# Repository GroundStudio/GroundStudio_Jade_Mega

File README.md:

GroundStudio Jade Mega
====================================

Get it from [ardushop.ro](https://ardushop.ro/en/development-boards/1937-groundstudio-jade-m1-6427854029508.html)

Explore all the GroundStudio products at [ardushop.ro](https://ardushop.ro/en/37-groundstudio)

Description
-------------------
ATMEGA2560 based development board with 256kBytes of In-System Self-Programmable Flash program memory, 4kBytes EEPROM, 8kBytes Internal SRAM, 15 PWM Channels, 70 Digital Pins including 16 channel 10 bit ADC Pins and HT42B534 for USB comunication.

Contents
-------------------

* [/Documentation](https://github.com/GroundStudio/GroundStudio_Jade_Mega/tree/main/Documentation) -- Pinout.
* [/Hardware](https://github.com/GroundStudio/GroundStudio_Jade_Mega/tree/main/Hardware) -- Schematics, layout.

Versions
-------------------
*(Not all tags shown)*

- [REV 0.1]

License
-------------------

This is released under the [Attribution-ShareAlike 4.0 International (CC BY-SA 4.0)](https://creativecommons.org/licenses/by-sa/4.0/) license.
**You are welcome to use this for commercial purposes.**

Please consider contributing back to this project or others to help the open-source hardware community continue to thrive and grow!

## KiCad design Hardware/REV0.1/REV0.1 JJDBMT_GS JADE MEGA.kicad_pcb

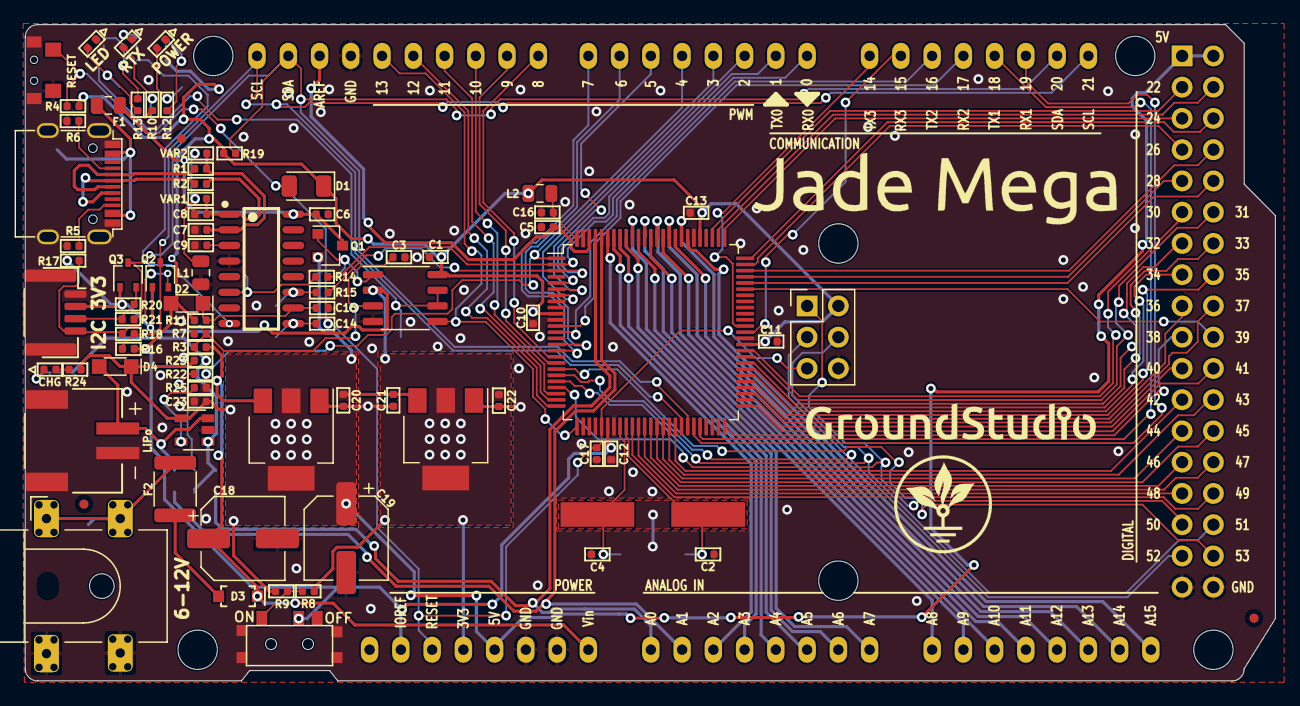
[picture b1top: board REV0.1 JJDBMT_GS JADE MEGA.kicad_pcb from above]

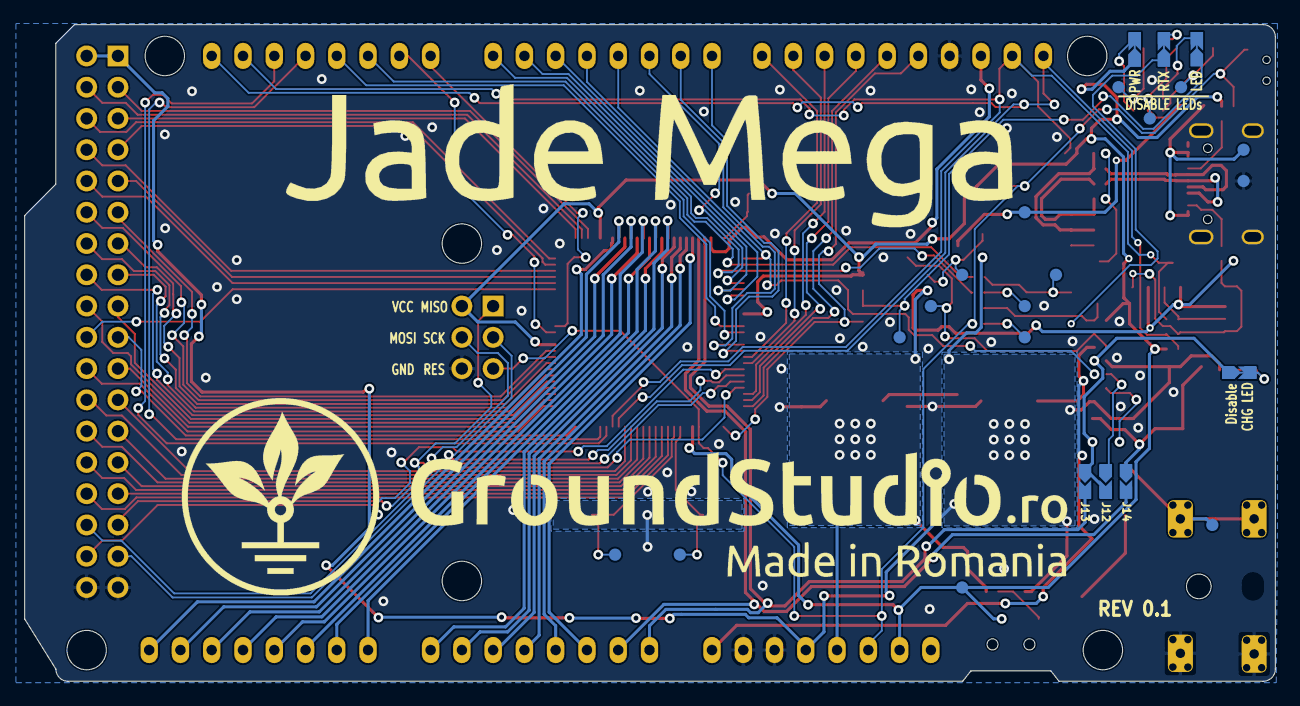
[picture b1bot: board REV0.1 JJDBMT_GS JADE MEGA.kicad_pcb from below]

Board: 2 copper layers, 101.6 x 53.3 mm, 112 parts (7 on the bottom side), 115 nets.

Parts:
C1, C3, C5, C6, C10, C11, C12, C13, C14, C15, C16, C20: C_0402_100nF_16V; C_0402_1005Metric
C2, C4, C17: C_0402_22pF_50V; C_0402_1005Metric
C7, C8: C_0402_47pF_50V; C_0402_1005Metric
C9, C23: C_0402_1uF_10V; C_0402_1005Metric
C18, C19: CP_Elec_6.3x5.4_47uF_25V; CP_Elec_6.3x5.4
C21, C22: C_0402_10uF_10V; C_0402_1005Metric
D1: D_1206_CD1206-S01575; D_1206_3216Metric
D2, D4: SOD-323 SD103AWS; SOD-323
D3: SOD-123 1N4007W; SOD-123
D5: LED_0402_RED; LED_0402_1005Metric
F1: Fuse_0805_MF-PSMF050X-2; Fuse_0805_2012Metric
F2: Fuse_1812_MF-MSMF050-2; Fuse_1812_4532Metric
FID1, FID2, FID3: Fiducial; Fiducial_0.75mm_Mask1.5mm
IC1: SOP-16_150MIL HT42B534-2; SOP-16_150MIL
IC2: SOT23-5 BRCL4054CME; SOT-23-5
J1: RX/TX LED DISABLE; SolderJumper_NC
J2: PWR LED DISABLE; SolderJumper_NC
J3: L LED DISABLE; SolderJumper_NC
J4: Conn_02x03_Odd_Even; PinHeader_2x03_P2.54mm_Vertical_Male
J5: Conn_01x10; PinHeader_1x10_P2.54mm_Vertical_Female
J6, J7, J9, J10, J11: Conn_01x08; PinHeader_1x08_P2.54mm_Vertical_Female
J8: Conn_02x18; PinHeader_2x18_P2.54mm_Vertical_Male
J12: CONNECT & SET D4 HIGH TO READ CHRG LVL ON A0; SolderJumper_NO
J13: CONNECT TO READ CHRG LVL ON A0; SolderJumper_NO
J14: CONNECT TO READ BATT LVL ON A1; SolderJumper_NO
J15: DC-005-5.5-Barr_Jck_SMD; DC-005-5.5-2.0MM-SMD
J16: SolderJumper_NC
L1: L_0805_BLM21PG221SN1D; L_0805_2012Metric
L2: L_0805_SCMI201209X100KT; L_0805_2012Metric
LED1, LED3: LED_0402_GREEN; LED_0402_1005Metric
LED2: LED_0402_RED; LED_0402_1005Metric
Q1: SOT-23 IRLML6402; SOT-23
Q2, Q3: SOT-323 2N7002PW; SOT-323_SC-70
R1, R2: R_0402_33; R_0402_1005Metric
R3, R4, R7: R_0402_10k; R_0402_1005Metric
R5, R6: R_0402_5.1k; R_0402_1005Metric
R8: DNP; R_0402_1005Metric
R9, R11, R18, R21: R_0402_0; R_0402_1005Metric
R10, R12, R13, R24: R_0402_20k; R_0402_1005Metric
R14, R15: R_0402_1k; R_0402_1005Metric
R16, R17, R19, R20: R_0402_2.2k; R_0402_1005Metric
R22, R25: R_0402_2k; R_0402_1005Metric
R23: R_0402_820k; R_0402_1005Metric
SW1: K3-1296S-E2
SW2: TS24CA
TP1: TP_VBUS; TestPoint
TP2: TP_USB_VCC; TestPoint
TP3: TP_LCMD; TestPoint
TP4: TP_VCC; TestPoint
TP5: TP_CMP; TestPoint
TP6: TP_GATE; TestPoint
TP7: TP_XT1; TestPoint
TP8: TP_USH; TestPoint
TP9: TP_XT2; TestPoint
TP10: TP_RTXL; TestPoint
TP11: TP_DTR; TestPoint
TP12: TP_ONL; TestPoint
TP13: TP_LL; TestPoint
TP14: TP_TX; TestPoint
TP15: TP_RX; TestPoint
TP16: TP_PWRIN; TestPoint
U1: SOP-8_3.9x4.9_P1.27 LM358; SOP-8_3.9x4.9mm_P1.27mm
U2: ATMEGA2560-16AU; TQFP-100_14x14mm_P0.5mm
U3: SOT-223 AMS1117-5.0; SOT-223
U4: SOT-223 AMS1117-3.3; SOT-223
USB1: USB_C 918-418K2023S40001; USB_C_C167321
VAR1, VAR2: R_0402_PS0402V014AT; R_0402_1005Metric
X1: SH_1x04_P1.0_H; SH__1x04_P1.00mm_Horizontal
X2: PH__1x02_P2.0_H; PH__1x02_P2.00mm_Horizontal
Y1: HC49-SMD 5M0-1600A2020; Crystal_HC49-SMD

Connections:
+3V3: C22.1, J9.5, Q2.1, Q3.1, R8.2, R17.1, R20.2, U1.2, U4.2, U4.4, X1.2
+5V: C19.1, C20.1, C21.1, C23.1, D4.1, IC2.4, J8.1, J8.2, J9.4, Q1.2, R9.1, R23.1, R24.2, U3.2, U3.4, U4.3
+BAT: D4.2, IC2.3, J14.1, X2.2
A0: J10.8, J13.2, U2.97
A1: J10.7, J14.2, U2.96
A2: J10.6, U2.95
A3: J10.5, U2.94
A4: J10.4, U2.93
A5: J10.3, U2.92
A6: J10.2, U2.91
A7: J10.1, U2.90
A8: J11.8, U2.89
A9: J11.7, U2.88
A10: J11.6, U2.87
A11: J11.5, U2.86
A12: J11.4, U2.85
A13: J11.3, U2.84
A14: J11.2, U2.83
A15: J11.1, U2.82
AREF: C5.1, J5.3, U2.98
CHRG: IC2.1, J12.2, J13.1, J16.1, R23.2
D2: J6.6, U2.6
D3: J6.5, U2.7
D4: J6.4, R22.1, U2.1
D5: J6.3, U2.5
D6: J6.2, U2.15
D7: J6.1, U2.16
D8: J5.10, U2.17
D9: J5.9, U2.18
D10: J5.8, U2.23
D11: J5.7, U2.24
D12: J5.6, U2.25
D13_SCK: J5.5, U1.5, U2.26
D22: J8.3, U2.78
D23: J8.4, U2.77
D24: J8.5, U2.76
D25: J8.6, U2.75
D26: J8.7, U2.74
D27: J8.8, U2.73
D28: J8.9, U2.72
D29: J8.10, U2.71
D30: J8.11, U2.60
D31: J8.12, U2.59
D32: J8.13, U2.58
D33: J8.14, U2.57
D34: J8.15, U2.56
D35: J8.16, U2.55
D36: J8.17, U2.54
D37: J8.18, U2.53
D38: J8.19, U2.50
D39: J8.20, U2.70
D40: J8.21, U2.52
D41: J8.22, U2.51
D42: J8.23, U2.42
D43: J8.24, U2.41
D44: J8.25, U2.40
D45: J8.26, U2.39
D46: J8.27, U2.38
D47: J8.28, U2.37
D48: J8.29, U2.36
D49: J8.30, U2.35
D50: J4.1, J8.31, U2.22
D51: J4.4, J8.32, U2.21
D52: J4.3, J8.33, U2.20
D53: J8.34, U2.19
D+: R2.2, USB1.A6, USB1.B6
D-: R1.2, USB1.A7, USB1.B7
GND: C1.2, C2.1, C3.2, C4.2, C5.2, C6.2, C7.1, C8.2, C9.2, C10.2, C11.2, C12.2, C13.2, C15.2, C16.1, C17.2, C18.2, C19.2, C20.2, C21.2, C22.2, C23.2, IC1.4, IC2.2, J4.6, J5.4, J8.35, J8.36, J9.2, J9.3, J15.3, J15.4, L1.1, LED2.1, LED3.1, R5.2, R6.2, R7.1, R25.1, SW2.1, SW2.2, SW2.3, TP8.~, U1.4, U2.11, U2.32, U2.62, U2.81, U2.99, U3.1, U4.1, USB1.0, USB1.A1, USB1.A12, USB1.B1, USB1.B12, X1.0, X1.1, X2.0, X2.1
IC1_RX: IC1.11, R15.2, TP15.~
IC1_TX: IC1.6, R14.2, TP14.~
L_CMD: J3.1, TP3.~, U1.6, U1.7
unnamed: C3.1, R3.1, R7.2, TP5.~, U1.3
unnamed: C9.1, IC1.3
unnamed: C14.1, IC1.9, TP11.~
unnamed: C15.1, D2.1, IC1.10, R11.2
unnamed: C16.2, L2.2, U2.100
unnamed: D3.2, F2.2
unnamed: D5.1, J16.2
unnamed: D5.2, R24.1
unnamed: F2.1, J15.5, TP16.~
unnamed: IC1.8, J1.1
unnamed: IC2.5, R25.2
unnamed: J1.2, LED1.1
unnamed: J2.2, R12.1
unnamed: J3.2, R13.1
unnamed: J12.1, R22.2
unnamed: L1.2, VAR1.2, VAR2.2
unnamed: LED1.2, R10.2, TP10.~
unnamed: LED2.2, R12.2, TP12.~
unnamed: LED3.2, R13.2, TP13.~
unnamed: Q1.1, TP6.~, U1.1
unnamed: Q2.2, R17.2, R18.1, X1.4
unnamed: Q3.2, R20.1, R21.1, X1.3
unnamed: R5.1, USB1.B5
unnamed: R6.1, USB1.A5
unnamed: R8.1, R9.2, SW1.3
RESET: C14.2, C17.1, D1.2, J4.5, J9.6, R4.1, SW2.4, U2.30
RXD0: J6.8, R14.1, U2.2
RXD1: J7.6, U2.45
RXD2: J7.4, U2.12
RXD3: J7.2, U2.63
SCL: J5.1, J7.8, Q2.3, R16.1, R18.2, U2.43
SDA: J5.2, J7.7, Q3.3, R19.1, R21.2, U2.44
TXD0: J6.7, R15.1, U2.3
TXD1: J7.5, U2.46
TXD2: J7.3, U2.13
TXD3: J7.1, U2.64
UD+: C8.1, IC1.1, R2.1, VAR1.1
UD-: C7.2, IC1.2, R1.1, VAR2.1
USB_VCC: C6.1, F1.1, IC1.16, Q1.3, R10.1, TP2.~
VBUS: F1.2, TP1.~, USB1.A4, USB1.A9, USB1.B4, USB1.B9
VCC: C1.1, C10.1, C11.1, C12.1, C13.1, D1.1, D2.2, J2.1, J4.2, J9.7, L2.1, R4.2, R11.1, R16.2, R19.2, SW1.2, TP4.~, U1.8, U2.10, U2.31, U2.61, U2.80
VIN: C18.1, D3.1, J9.1, R3.2, U3.3
XTAL1: C2.2, TP7.~, U2.34, Y1.1
XTAL2: C4.1, TP9.~, U2.33, Y1.2

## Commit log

2022-08-11 - initial commit
2022-08-26 - added schematic pdf file
2022-08-26 - added "Kicad6" to revision folder name
2023-03-15 Update README.md
    - removed references to "library"
2023-10-26 - added .step 3D file of the board
2024-03-20 - fixed missplaced labels of MOSI and SS
2025-04-27 Update shop links
    Old URIs were nolonger valid, updated with the working URIs
2025-09-10 update shop links
